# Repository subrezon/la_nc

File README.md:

# This keyboard has been succeeded by [Lancer](https://github.com/subrezon/lancer). If you're interested in la_nc - I recommend building a Lancer instead.

# la_nc

Inspired by keyboards like Planck, Lumberjack and Lesovoz, la_nc aims to deliver a lightly split, ortho typing experience in a similar footprint, as well as an easy build process.

The name comes from the design process: take a Planck, remove a column from each side, then split it down the middle. Planck -> lanc -> la_nc.

# Features

- 42 keys in a unique take on ortholinear layouts
- Supports MX switches through Kailh hotswap sockets, with reinforced ai03's antishear socket pads
- Powered by a ProMicro or a compatible MCU board
- Optional support for an SSD1306 OLED screen

# BOM

- PCB
- top plate
- bottom plate
- ProMicro compatible MCU board
- 42x SMD diodes (1N4148W SOD123)
- 42x Kailh hotswap sockets
- 1x 3x6mm 2-pin tactile reset button
- 16x M2x5 screws
- 8x M2x8 standoffs
- 42x MX switches
- 42x 1U keycaps

Optionally:

- ProMicro socket (24-pin wide)
- SSD1306 128x32 OLED screen
- OLED socket (4-pin)

# Build guide

TODO

# QMK Firmware

You can find the firmware under subrezon/la_nc in the official QMK repository: https://github.com/qmk/qmk_firmware/tree/master/keyboards/subrezon/la_nc

Here's an example of flashing the keyboard with the default firmware:

	make subrezon/la_nc:default:flash

Or, using the QMK CLI:

	qmk flash -kb subrezon/la_nc -km default

If you're unsure what to do with this information, check out the [QMK Documentation](https://docs.qmk.fm/#/) for information on how to get started with QMK.

If you're building la_nc without the OLED screen, make sure to disable it in the rules.mk of your keymap:

	OLED_ENABLE = false

# Coming soon

- Build guide
- Acrylic cover for the gap in the middle
- Soldered PCB option (MX, Alps, Choc)
- Hotswap Choc support
- OR, Support for 2U keys in the bottom row
- High & Low profile 3D-printable cases

# Special thanks

- ai03 and foostan - for the Kicad libraries
- The r/MechanicalKeyboards and r/ErgoMechKeyboards - for the feedback, critique and support

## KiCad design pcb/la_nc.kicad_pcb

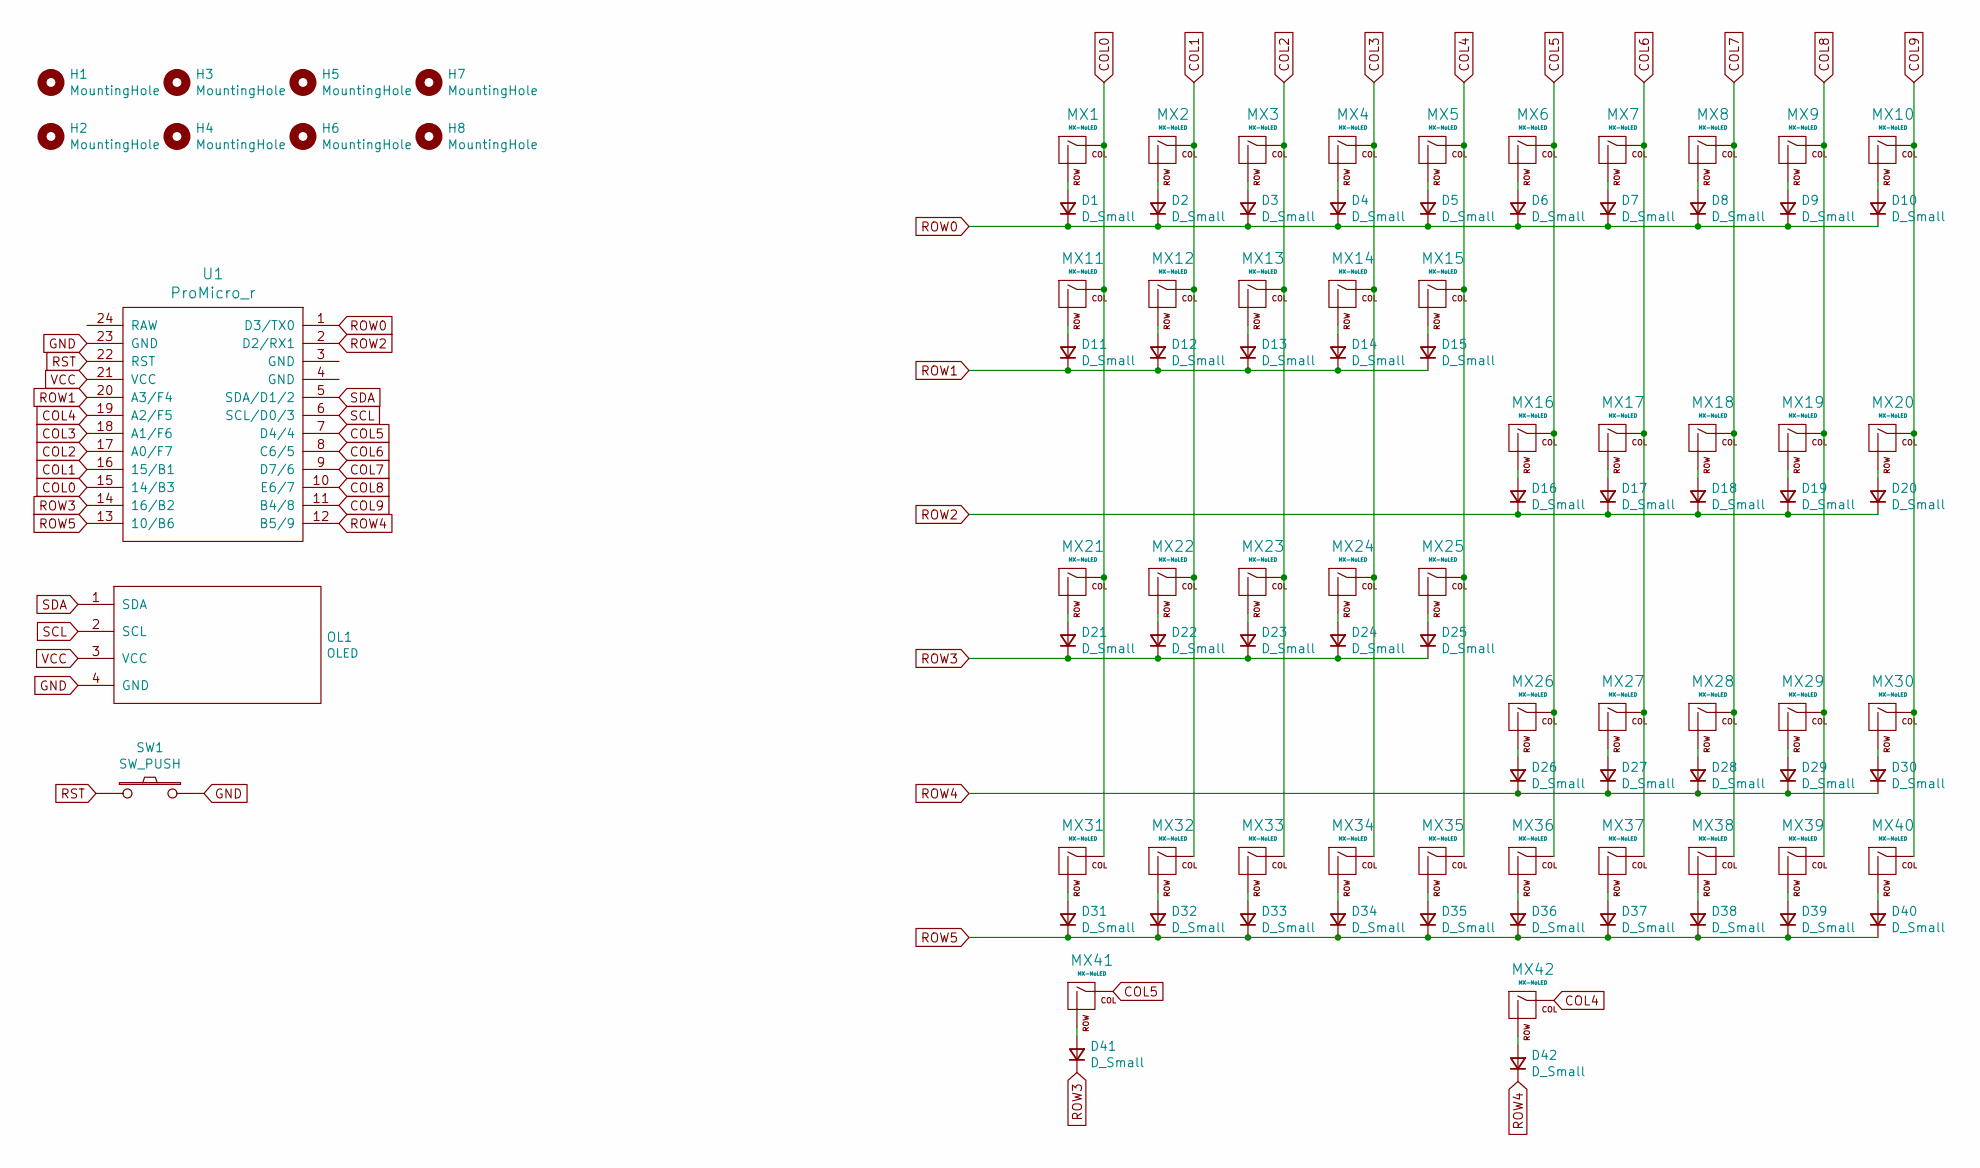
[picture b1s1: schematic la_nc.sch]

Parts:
D1, D2, D3, D4, D5, D6, D7, D8, D9, D10, D11, D12, D13, D14, D15, D16, D17, D18, D19, D20, D21, D22, D23, D24, D25, D26, D27, D28, D29, D30, D31, D32, D33, D34, D35, D36, D37, D38, D39, D40, D41, D42: D_Small; D3_SMD_v2
H1, H2, H3, H4, H5, H6, H7, H8: MountingHole; HOLE
MX1, MX2, MX3, MX4, MX5, MX6, MX7, MX8, MX9, MX10, MX11, MX12, MX13, MX14, MX15, MX16, MX17, MX18, MX19, MX20, MX21, MX22, MX23, MX24, MX25, MX26, MX27, MX28, MX29, MX30, MX31, MX32, MX33, MX34, MX35, MX36, MX37, MX38, MX39, MX40, MX41, MX42: MX-NoLED; MXOnly-1U-Hotswap-Antishear
OL1: OLED; OLED_v2
SW1: SW_PUSH; ResetSW_1side
U1: ProMicro_r; ProMicro_v3.5

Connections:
COL0: MX1.1 (COL), MX11.1 (COL), MX21.1 (COL), MX31.1 (COL), U1.15 (14/B3)
COL1: MX2.1 (COL), MX12.1 (COL), MX22.1 (COL), MX32.1 (COL), U1.16 (15/B1)
COL2: MX3.1 (COL), MX13.1 (COL), MX23.1 (COL), MX33.1 (COL), U1.17 (A0/F7)
COL3: MX4.1 (COL), MX14.1 (COL), MX24.1 (COL), MX34.1 (COL), U1.18 (A1/F6)
COL4: MX5.1 (COL), MX15.1 (COL), MX25.1 (COL), MX35.1 (COL), MX42.1 (COL), U1.19 (A2/F5)
COL5: MX6.1 (COL), MX16.1 (COL), MX26.1 (COL), MX36.1 (COL), MX41.1 (COL), U1.7 (D4/4)
COL6: MX7.1 (COL), MX17.1 (COL), MX27.1 (COL), MX37.1 (COL), U1.8 (C6/5)
COL7: MX8.1 (COL), MX18.1 (COL), MX28.1 (COL), MX38.1 (COL), U1.9 (D7/6)
COL8: MX9.1 (COL), MX19.1 (COL), MX29.1 (COL), MX39.1 (COL), U1.10 (E6/7)
COL9: MX10.1 (COL), MX20.1 (COL), MX30.1 (COL), MX40.1 (COL), U1.11 (B4/8)
GND: OL1.4 (GND), SW1.2, U1.23 (GND)
unnamed: D1.2 (A), MX1.2 (ROW)
unnamed: D2.2 (A), MX2.2 (ROW)
unnamed: D3.2 (A), MX3.2 (ROW)
unnamed: D4.2 (A), MX4.2 (ROW)
unnamed: D5.2 (A), MX5.2 (ROW)
unnamed: D6.2 (A), MX6.2 (ROW)
unnamed: D7.2 (A), MX7.2 (ROW)
unnamed: D8.2 (A), MX8.2 (ROW)
unnamed: D9.2 (A), MX9.2 (ROW)
unnamed: D10.2 (A), MX10.2 (ROW)
unnamed: D11.2 (A), MX11.2 (ROW)
unnamed: D12.2 (A), MX12.2 (ROW)
unnamed: D13.2 (A), MX13.2 (ROW)
unnamed: D14.2 (A), MX14.2 (ROW)
unnamed: D15.2 (A), MX15.2 (ROW)
unnamed: D16.2 (A), MX16.2 (ROW)
unnamed: D17.2 (A), MX17.2 (ROW)
unnamed: D18.2 (A), MX18.2 (ROW)
unnamed: D19.2 (A), MX19.2 (ROW)
unnamed: D20.2 (A), MX20.2 (ROW)
unnamed: D21.2 (A), MX21.2 (ROW)
unnamed: D22.2 (A), MX22.2 (ROW)
unnamed: D23.2 (A), MX23.2 (ROW)
unnamed: D24.2 (A), MX24.2 (ROW)
unnamed: D25.2 (A), MX25.2 (ROW)
unnamed: D26.2 (A), MX26.2 (ROW)
unnamed: D27.2 (A), MX27.2 (ROW)
unnamed: D28.2 (A), MX28.2 (ROW)
unnamed: D29.2 (A), MX29.2 (ROW)
unnamed: D30.2 (A), MX30.2 (ROW)
unnamed: D31.2 (A), MX31.2 (ROW)
unnamed: D32.2 (A), MX32.2 (ROW)
unnamed: D33.2 (A), MX33.2 (ROW)
unnamed: D34.2 (A), MX34.2 (ROW)
unnamed: D35.2 (A), MX35.2 (ROW)
unnamed: D36.2 (A), MX36.2 (ROW)
unnamed: D37.2 (A), MX37.2 (ROW)
unnamed: D38.2 (A), MX38.2 (ROW)
unnamed: D39.2 (A), MX39.2 (ROW)
unnamed: D40.2 (A), MX40.2 (ROW)
unnamed: D41.2 (A), MX41.2 (ROW)
unnamed: D42.2 (A), MX42.2 (ROW)
ROW0: D1.1 (K), D2.1 (K), D3.1 (K), D4.1 (K), D5.1 (K), D6.1 (K), D7.1 (K), D8.1 (K), D9.1 (K), D10.1 (K), U1.1 (D3/TX0)
ROW1: D11.1 (K), D12.1 (K), D13.1 (K), D14.1 (K), D15.1 (K), U1.20 (A3/F4)
ROW2: D16.1 (K), D17.1 (K), D18.1 (K), D19.1 (K), D20.1 (K), U1.2 (D2/RX1)
ROW3: D21.1 (K), D22.1 (K), D23.1 (K), D24.1 (K), D25.1 (K), D41.1 (K), U1.14 (16/B2)
ROW4: D26.1 (K), D27.1 (K), D28.1 (K), D29.1 (K), D30.1 (K), D42.1 (K), U1.12 (B5/9)
ROW5: D31.1 (K), D32.1 (K), D33.1 (K), D34.1 (K), D35.1 (K), D36.1 (K), D37.1 (K), D38.1 (K), D39.1 (K), D40.1 (K), U1.13 (10/B6)
RST: SW1.1, U1.22 (RST)
SCL: OL1.2 (SCL), U1.6 (SCL/D0/3)
SDA: OL1.1 (SDA), U1.5 (SDA/D1/2)
VCC: OL1.3 (VCC), U1.21 (VCC)

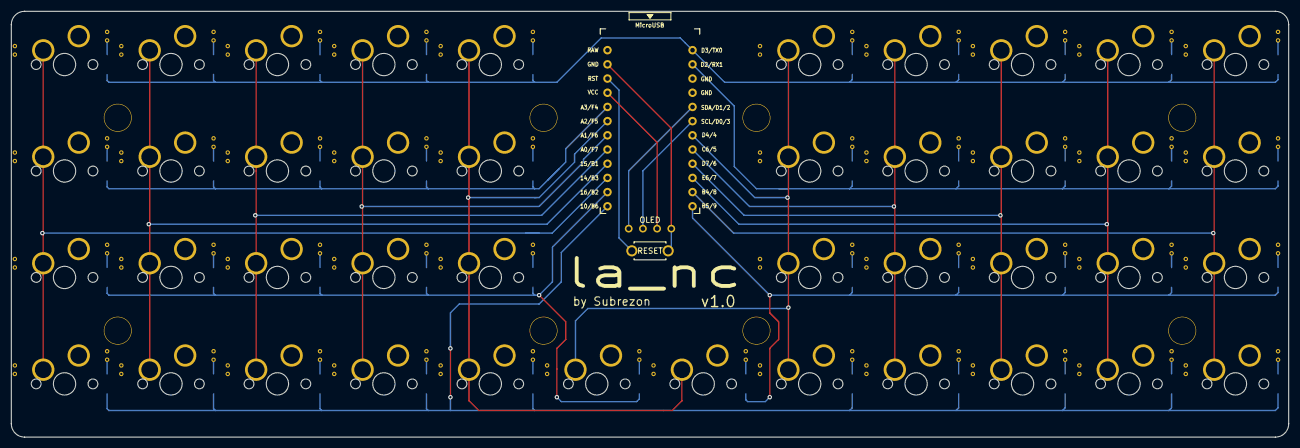
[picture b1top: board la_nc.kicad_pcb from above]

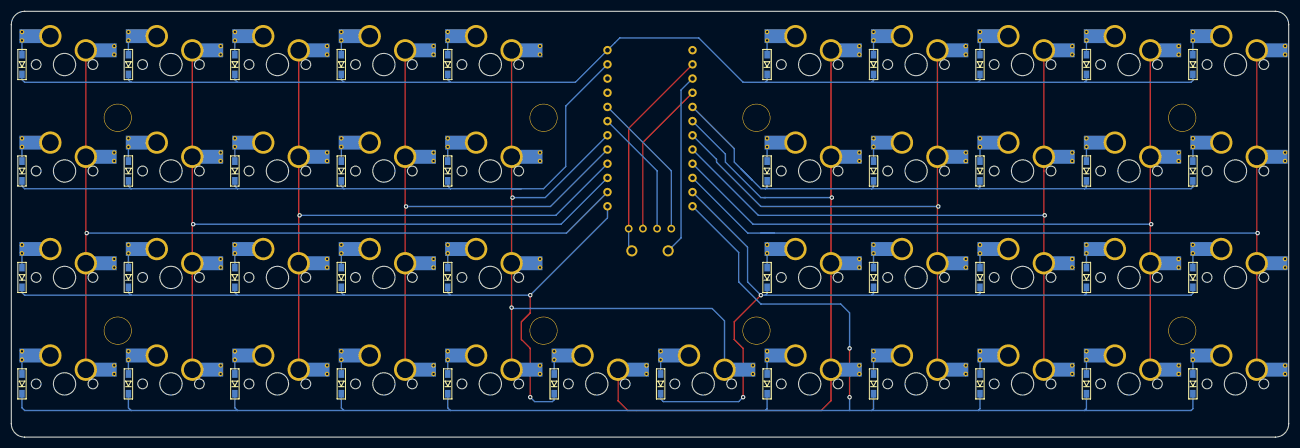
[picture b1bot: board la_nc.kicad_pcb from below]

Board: 2 copper layers, 228.6 x 76.2 mm, 95 parts (42 on the bottom side), 63 nets.

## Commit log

2022-03-25 created kicad project
2022-03-25 added submodules
2022-03-25 fixed + imported submodules
2022-03-30 prototype went to production
2022-03-30 pcb, plate, gerbers
2022-03-30 removed large text footprint
2022-04-11 license
2022-04-13 initial readme
2022-04-13 readme typo
2022-05-11 Update README.md
    Update about firmware
2022-05-12 Update README.md
    Firmware merged to official QMK
2023-05-08 lancer ad
